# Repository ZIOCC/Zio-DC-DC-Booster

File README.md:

# Zio DC-DC Booster

> This product can be available for purchase [here](https://www.smart-prototyping.com/Zio-DC-DC-Booster).

#### Description

The Zio DC-DC is an adjustable voltage booster that can take a 3.7v to 10v input and boost any higher voltage between 5v and 12.5v.

The board features four connectors (one set of screw terminals, two JST PH connectors, and a micro-USB connector) on the input bus, and a set of screw terminals and PTH pads for the output.

Output voltage is adjusted using a potentiometer that can be adjusted with a Phillips or 2mm flathead screwdriver. The 24-segment (3 seven-segment digits and three decimal indicators) display can be toggled using a momentary switch to show the input voltage or output voltage, and a second momentary switch toggles the output on and off.

> Note: This board can only boost, and doesn’t have the ability to regulate the input to lower voltage.

#### Specification

* Booster IC: TPS61088
* Input: 3.7v to 10v
* Output: 5v to 12.5v
* Dimension: 46.8x 56.7mm
* Weight: 20.7g

#### Links

* [Eagle and Schematic file](https://github.com/ZIOCC/Zio-DC-DC-Booster)
* [TPS61088 Datasheet](http://www.ti.com/product/TPS61088/technicaldocuments)
* [Firmware for STM8](https://www.smart-prototyping.com/image/data/NOA-RnD/101917%20DC-DC%20Booster/Zio%20DC-DC%20Booster_firmware.zip)

> ###### About Zio
> Zio is a new line of open sourced, compact, and grid layout boards, fully integrated for Arduino and Qwiic ecosystem. Designed ideally for wearables, robotics, small-space limitations or other on the go projects. Check out other awesome Zio products [here](https://www.smart-prototyping.com/Zio).

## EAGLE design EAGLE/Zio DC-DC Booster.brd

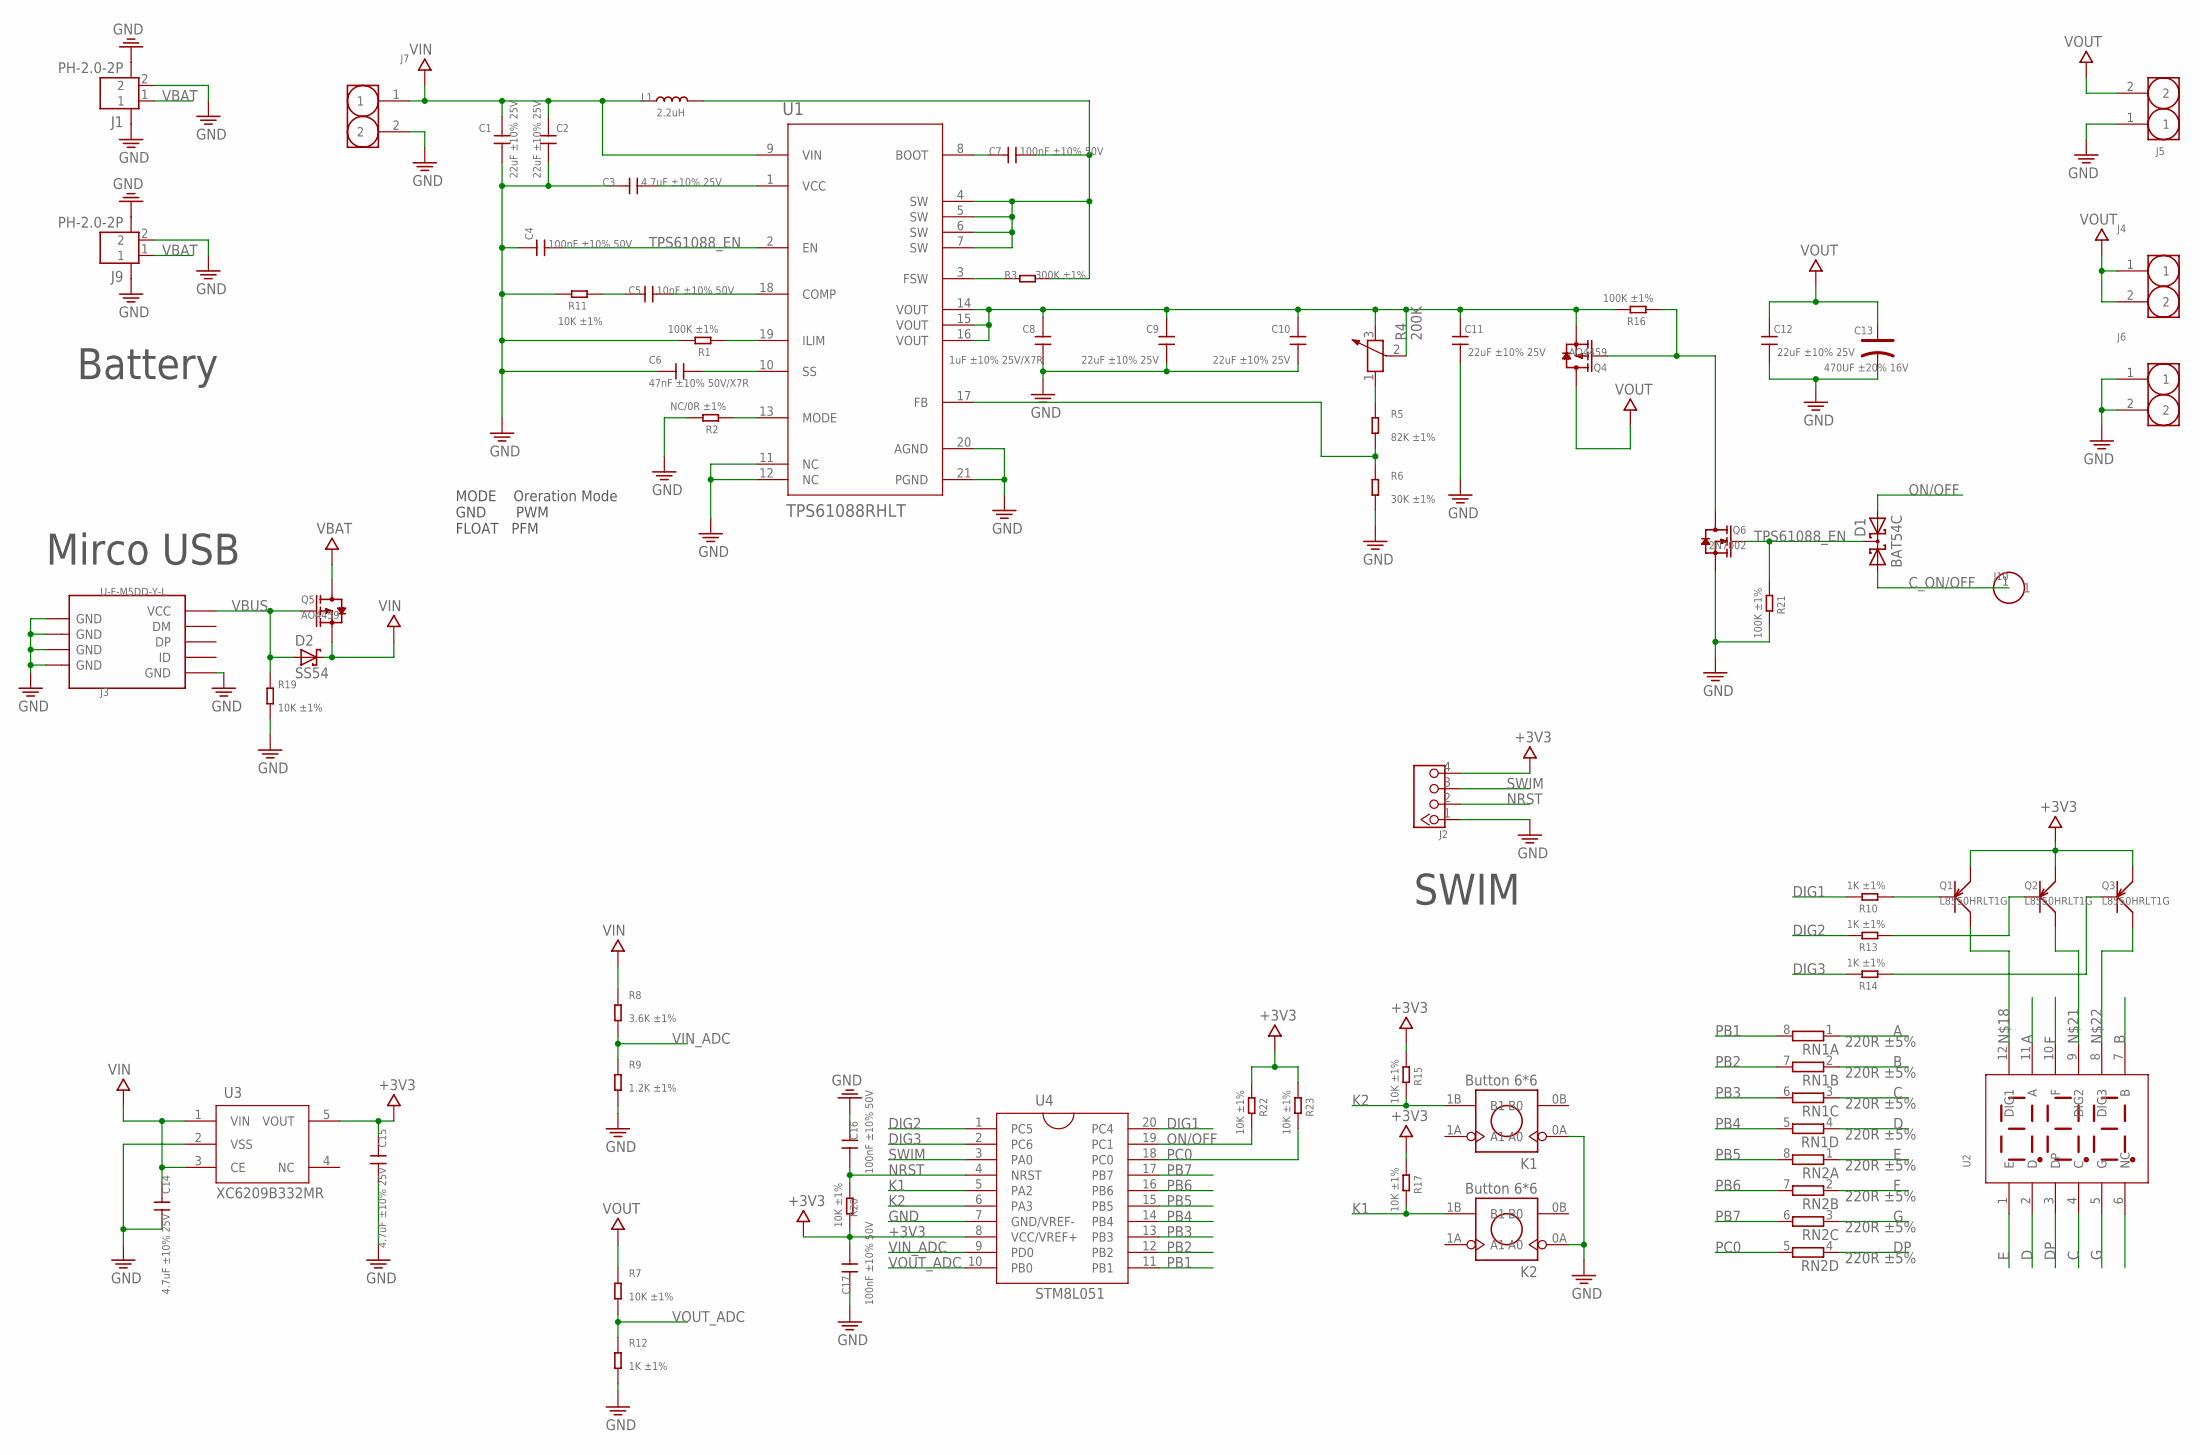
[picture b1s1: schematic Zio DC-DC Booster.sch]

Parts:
C1, C2, C9, C10, C11, C12: 22uF ±10% 25V; 1206
C3, C14, C15: 4.7uF ±10% 25V; 0603
C4, C7, C16, C17: 100nF ±10% 50V; 0603
C5: 10nF ±10% 50V; 0603
C6: 47nF ±10% 50V/X7R; 0603
C8: 1uF ±10% 25V/X7R; 0603
C13: 470UF ±20% 16V; ELECTRO-SMD-E-7.8MM
D1: BAT54C; SOT23
D2: SS54; SMA
J1, J9: PH-2.0-2P
J2: HEADER-4P-TEST_3.08_4P; TEST_3.08_4P
J3: U-F-M5DD-Y-L; MICRO-SMD
J4, J6: HEADER-2P-65/35MIL; 2P-2.54-65/35MIL
J5, J7: HEADER-2P-SCREW5.0; 2P-SCREW-5.0
J10: HEADER-1P; 1P-40MIL
K1, K2: Button 6*6; 4P-SMD-6X6
L1: 2.2uH; L-10.5*11.5
Q1, Q2, Q3: L8550HRLT1G; SOT23
Q4, Q5: AO4459; SOP08
Q6: 2N7002; SOT23
R1, R16, R21: 100K ±1%; 0603
R2: NC/0R ±1%; 0402
R3: 300K ±1%; 0603
R4: 200K; 3P-SQUA-7X6.8
R5: 82K ±1%; 0603
R6: 30K ±1%; 0603
R7, R11, R15, R17, R19, R20, R22, R23: 10K ±1%; 0603
R8: 3.6K ±1%; 0603
R9: 1.2K ±1%; 0603
R10, R12, R13, R14: 1K ±1%; 0603
RN1, RN2: 220R ±5%; RESISTOR-DIL_0603-ARC
U1: TPS61088RHLT; IC_RHL0020A
U2: SEGMENT_ANODES_3_0.28
U3: XC6209B332MR; SOT23-5
U4: STM8L051; TSSOP20

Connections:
+3V3: C15.1, C17.1, J2.4, Q1.2 (E), Q2.2 (E), Q3.2 (E), R15.2, R17.2, R20.2, R22.2, R23.2, U3.5 (VOUT), U4.8 (VCC/VREF+)
A: RN1.1, U2.11 (A)
B: RN1.2 (1), U2.7 (B)
C: RN1.3 (1), U2.4 (C)
C_ON/OFF: D1.1 (A1), J10.1
D: RN1.4 (1), U2.2 (D)
DIG1: R10.1, U4.20 (PC4)
DIG2: R13.1, U4.1 (PC5)
DIG3: R14.1, U4.2 (PC6)
DP: RN2.4 (1), U2.3 (DP)
E: RN2.1, U2.1 (E)
F: RN2.2 (1), U2.10 (F)
G: RN2.3 (1), U2.5 (G)
GND: C1.2, C2.2, C3.1, C4.1, C6.1, C8.2, C9.2, C10.2, C11.2, C12.2, C13.-, C14.2, C15.2, C16.1, C17.2, J1.2, J1.7 (3), J1.8 (4), J2.1, J3.GND, J3.S1 (GND), J3.S1@1 (GND), J3.S1@2 (GND), J3.S2 (GND), J3.S2@1 (GND), J3.S2@2 (GND), J3.S3 (GND), J3.S3@1 (GND), J3.S3@2 (GND), J3.S4 (GND), J3.S4@1 (GND), J3.S4@2 (GND), J5.1, J6.1, J6.2, J7.2, J9.2, J9.7 (3), J9.8 (4), K1.0A (A0), K2.0A (A0), Q6.2 (S), R1.1, R2.1, R6.2, R9.1, R11.1, R12.1, R19.2, R21.1, U1.11 (NC), U1.12 (NC), U1.20 (AGND), U1.21 (PGND), U3.2 (VSS), U4.7 (GND/VREF-)
K1: K2.1B (B1), R17.1, U4.5 (PA2)
K2: K1.1B (B1), R15.1, U4.6 (PA3)
unnamed: R4.1, R5.1
unnamed: Q1.1 (B), R10.2
unnamed: Q2.1 (B), R13.2
unnamed: Q3.1 (B), R14.2
unnamed: Q4.4 (G), Q6.3 (D), R16.2
unnamed: C5.1, R11.2
unnamed: C5.2, U1.18 (COMP)
unnamed: Q1.3 (C), U2.12 (DIG1)
unnamed: Q2.3 (C), U2.9 (DIG2)
unnamed: Q3.3 (C), U2.8 (DIG3)
unnamed: C3.2, U1.1 (VCC)
unnamed: C7.1, U1.8 (BOOT)
unnamed: R3.1, U1.3 (FSW)
unnamed: R5.2, R6.1, U1.17 (FB)
unnamed: R2.2, U1.13 (MODE)
unnamed: C6.2, U1.10 (SS)
unnamed: R1.2, U1.19 (ILIM)
NRST: C16.2, J2.2, R20.1, U4.4 (NRST)
ON/OFF: D1.2 (A2), R22.1, U4.19 (PC1)
PB1: RN1.8 (2), U4.11 (PB1)
PB2: RN1.7 (2), U4.12 (PB2)
PB3: RN1.6 (2), U4.13 (PB3)
PB4: RN1.5 (2), U4.14 (PB4)
PB5: RN2.8 (2), U4.15 (PB5)
PB6: RN2.7 (2), U4.16 (PB6)
PB7: RN2.6 (2), U4.17 (PB7)
PC0: R23.1, RN2.5 (2), U4.18 (PC0)
SW: C7.2, L1.2, R3.2, U1.4 (SW), U1.5 (SW), U1.6 (SW), U1.7 (SW)
SWIM: J2.3, U4.3 (PA0)
TPS61088_EN: C4.2, D1.3 (CC), Q6.1 (G), R21.2, U1.2 (EN)
VBAT: J1.1, J9.1, Q5.5 (D), Q5.6 (D), Q5.7 (D), Q5.8 (D)
VBUS: D2.P$2 (A), J3.VBUS (VCC), Q5.4 (G), R19.1
VIN: C1.1, C2.1, C14.1, D2.P$1 (C), J7.1, L1.1, Q5.1 (S), Q5.2 (S), Q5.3 (S), R8.2, U1.9 (VIN), U3.1 (VIN), U3.3 (CE)
VIN_ADC: R8.1, R9.2, U4.9 (PD0)
VOUT: C12.1, C13.+, J4.1, J4.2, J5.2, Q4.5 (D), Q4.6 (D), Q4.7 (D), Q4.8 (D), R7.2
VOUT_ADC: R7.1, R12.2, U4.10 (PB0)
V_OUT: C8.1, C9.1, C10.1, C11.1, Q4.1 (S), Q4.2 (S), Q4.3 (S), R4.2, R4.3, R16.1, U1.14 (VOUT), U1.15 (VOUT), U1.16 (VOUT)

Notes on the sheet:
Battery
SWIM
Mirco USB
MODE Oreration Mode GND PWM FLOAT PFM

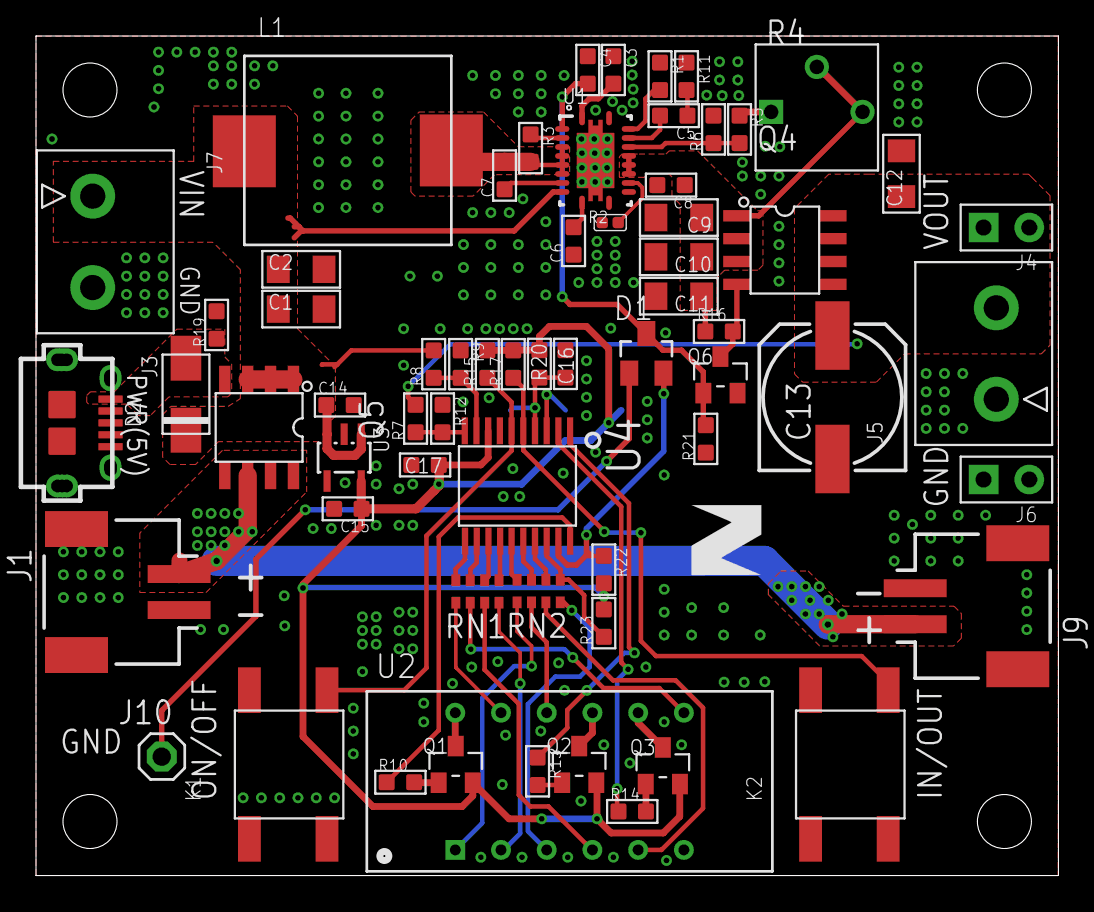
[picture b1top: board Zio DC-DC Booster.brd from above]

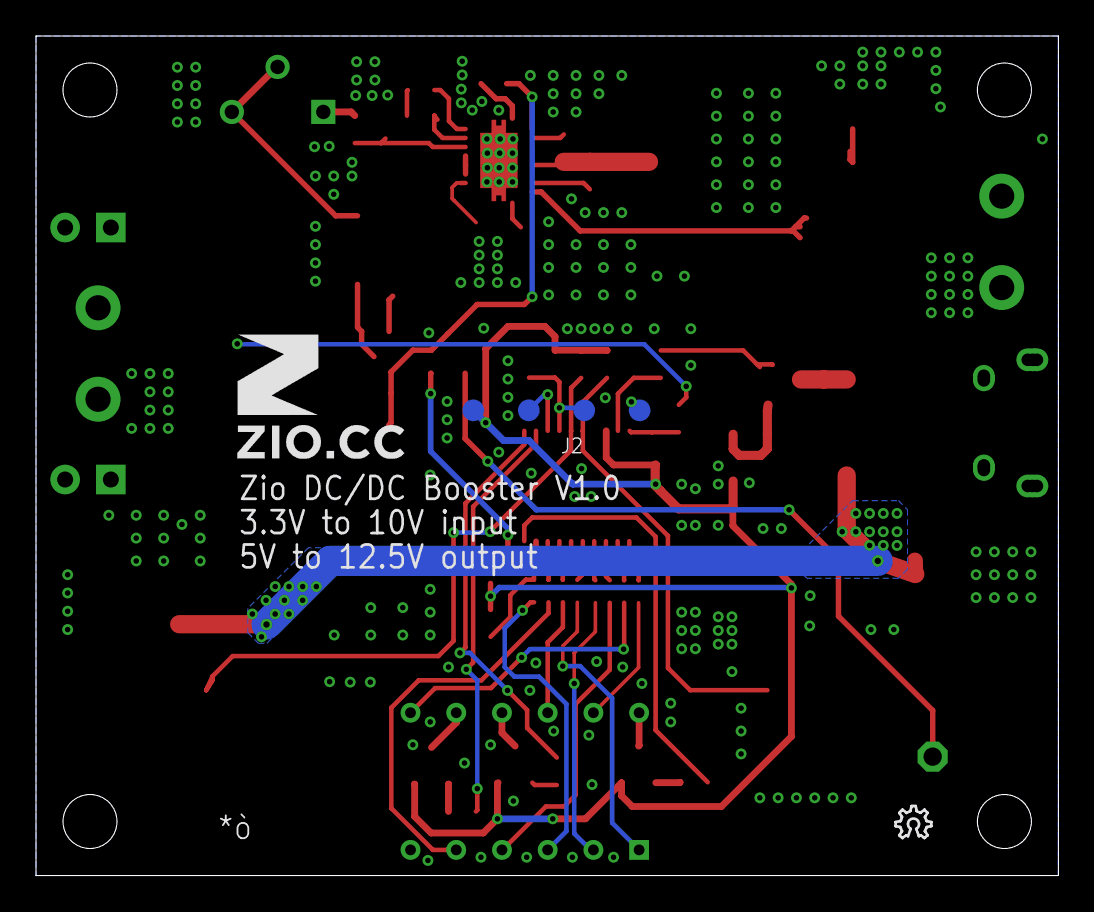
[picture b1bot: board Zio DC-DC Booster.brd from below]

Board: 2 copper layers, 56.8 x 46.6 mm, 68 parts (3 on the bottom side), 53 nets.

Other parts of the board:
LOGO1: LOGO-OSHW-6MILX0070-NT; OSHW_6X70_NOTEXT
U$2: 6MM
U$3: 7MM
